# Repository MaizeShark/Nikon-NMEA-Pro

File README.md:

# Nikon-NMEA-Pro

A low-power GNSS logger and BLE remote shutter for Nikon cameras with the 10-pin connector. It is a work in progress: the hardware is designed, the PCB has not been built or tested, and the firmware has not been started.

<p align="center"><em>Front (left) and back (right) of the PCB.</em></p>

## Goals

Older GPS units for Nikon cameras (GP-1, Solmeta GMAX) typically draw tens of mA continuously, are slow to get a cold fix, and have no wireless connectivity. This 35 x 35 mm module aims to improve on them:

- Standby draw of tens of µA instead of tens of mA
- Fast fixes by injecting assistance data (u-blox AssistNow) from a smartphone over BLE
- Four-constellation tracking with a u-blox M10 receiver
- BLE remote shutter and USB-C file access

| Status | Item |
| :--- | :--- |
| Done | Schematic and PCB layout |
| Pending | PCB fabrication and assembly |
| Pending | Power measurements (all current figures below are datasheet estimates) |
| Not started | Firmware |

## Camera connection

> [!NOTE]
> I connect the module to my Nikon D200 using a **Nikon MC-35 cable** (GPS adapter cable for RS232). I have not verified compatibility with other bodies or cables.

## Planned features

- **EXIF geotagging:** convert GNSS position and barometric altitude into 5 V TTL NMEA sentences for the camera.
- **Hot-shoe X-sync logging:** read the X-sync contact and write a `<wpt>` tag to the GPX log when the shutter fires.
- **Motion-aware track logging:** log GPX tracks to a 16 MB SPI NOR flash chip, pausing when the accelerometer shows the camera is stationary.
- **USB-C mass storage:** mount as a flash drive for drag-and-drop GPX access.
- **BLE remote:** trigger autofocus and shutter release from a smartphone app via MOSFET outputs.
- **Auto-wake:** monitor `V_CC` on the 10-pin connector and wake from System OFF when the camera powers on.

## Hardware

### Processing and communications

| Function | Part | Notes |
| :--- | :--- | :--- |
| MCU | u-blox BMD-340-A-R (nRF52840) | BLE, USB MSC, sensor fusion, NMEA generation |
| Level shifting | TI TXU0202 | 3V3 -> 5V for Camera UART |

### GNSS and sensors

- **Receiver:** u-blox MAX-M10S (GPS, Galileo, GLONASS, BeiDou concurrently).
- **Antenna:** active antenna on a U.FL connector, powered through a bias-T. A MOSFET driven by `LNA_EN` cuts antenna power when the GNSS is asleep.
- **Compass:** ST LSM303AGR (I2C), for tilt-compensated heading in `$--HDG` sentences.
- **Barometer:** Bosch BMP581 (I2C), for altitude.

### Power

The board can be powered from USB (5 V) or the camera (`V_BAT`, up to 8.4 V).

- **Source selection:** Nexperia BAV170 dual diode, chosen for very low reverse leakage to prevent backfeed.
- **Regulation:** TI TPS70933 3.3 V LDO. Accepts inputs above 30 V with about 1 µA quiescent current.
- **Backup:** Seiko MS621FE rechargeable coin cell, trickle-charged in normal use. It is intended to keep the u-blox RTC and orbital data alive for a few days with the camera battery removed, preserving fast fixes after a battery swap (about 4.5 days estimated).

## PCB

- **Size:** 35 x 35 mm, 4 layers.
- **Stackup:** JLC04161H-3313 (0.09 mm dielectric between L1 and L2).
- **RF:** 50 Ω coplanar waveguide with ground (CPWG) for the 1.5 GHz GNSS path.

### Assembly

Components are on both sides, so assembly is planned as two-stage soldering to keep the bottom side from shifting:

1. Bottom side (including hidden LGA pads): lead-free paste, reflowed on a hot plate at ~220 °C.
2. Top side: leaded paste, hot air at ~183 °C, below the bottom side's solidus so those joints stay solid.

## Estimated power budget

These are summed datasheet typical values, not measurements.

| State | Component | Current |
| :--- | :--- | :--- |
| Sleep | nRF52840 (System OFF) | ~1.0 µA |
| Sleep | MAX-M10S (software standby) | ~46.0 µA |
| Sleep | `V_BAT` ADC divider (3.2 MΩ) | ~2.6 µA |
| Sleep | I2C sensors, flash, LDO quiescent | ~3.8 µA |
| | **Total standby (estimated)** | **~53.4 µA** |
| Active | Full system (BLE, 4-GNSS, sensors, USB) | **~22 mA** |

At roughly 53 µA, standby would take over 3 years to drain a 1500 mAh battery, ignoring the battery's own self-discharge. Real numbers will be measured once the board is built.

## Firmware

Not started. The plan is Zephyr RTOS, with hardware interrupt handling, LittleFS wear leveling on the SPI flash, BLE GATT profiles, and USB mass storage.

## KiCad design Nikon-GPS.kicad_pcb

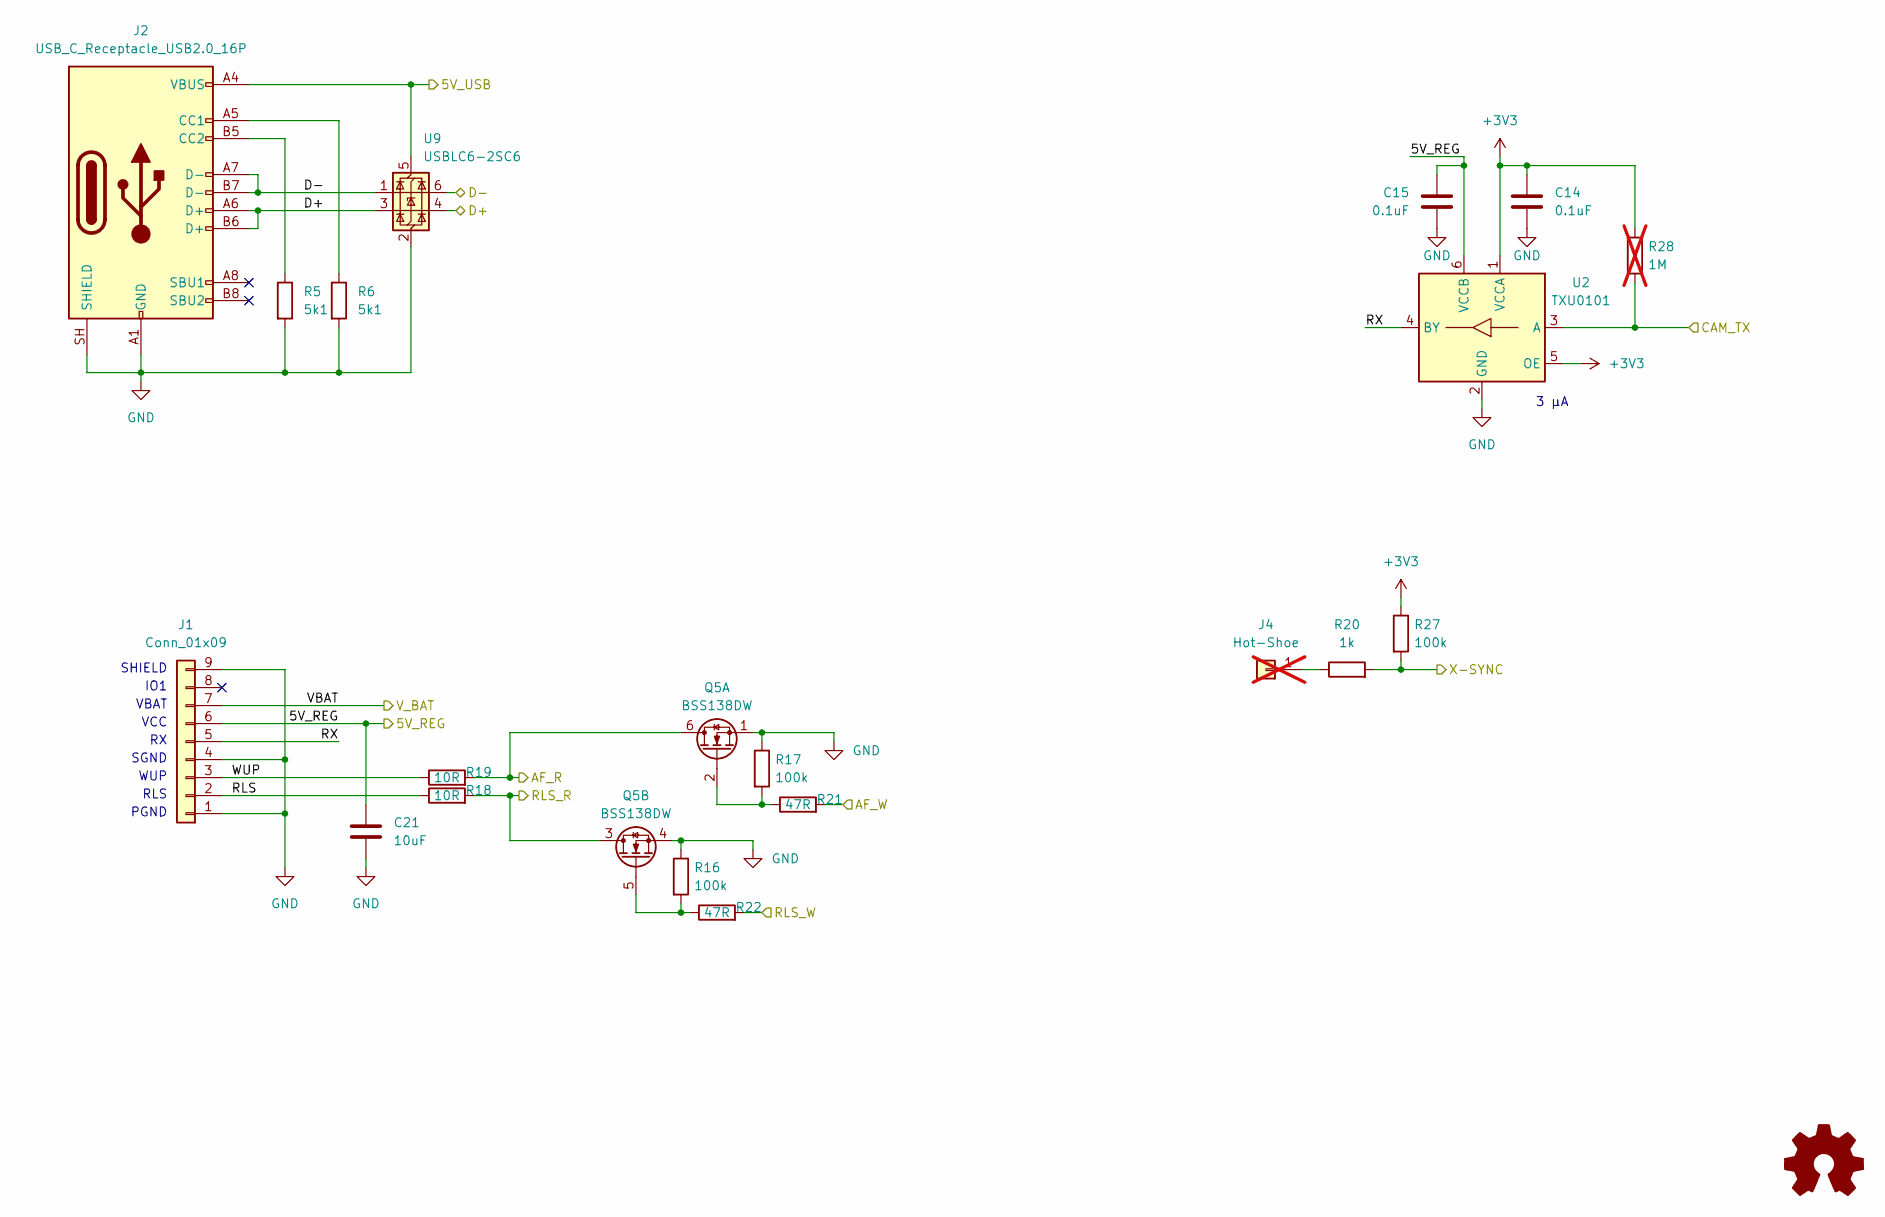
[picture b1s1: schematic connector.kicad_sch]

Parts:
C14, C15: 0.1uF; C_0402_1005Metric; LCSC C77020
C21: 10uF; C_0805_2012Metric; LCSC C32635
J1: Conn_01x09; Nikon Connector
J2: USB_C_Receptacle_USB2.0_16P; USB_C_Receptacle_G-Switch_GT-USB-7010ASV; LCSC C2988369
J4: Hot-Shoe; PinHeader_1x01_P2.54mm_Vertical; not fitted
Q5: BSS138DW; SOT-363_SC-70-6; LCSC C154900
R5, R6: 5k1; R_0402_1005Metric; LCSC C105872
R16, R17, R27: 100k; R_0402_1005Metric; LCSC C60491
R18, R19: 10R; R_0603_1608Metric; LCSC C109318
R20: 1k; R_0402_1005Metric; LCSC C106235
R21, R22: 47R; R_0402_1005Metric; LCSC C137973
R28: 1M; R_0402_1005Metric; LCSC C138033; not fitted
U2: TXU0101; Texas_DCK0006A_2.1x2mm_P0.65mm; LCSC C5217868
U9: USBLC6-2SC6; SOT-23-6; LCSC C5261088

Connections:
+3V3: C14.1, R27.1, R28.1, U2.1 (VCCA), U2.5 (OE); also elsewhere on the board
/Connector/5V_REG: C15.1, C21.1, J1.6, U2.6 (VCCB); also elsewhere on the board
/Connector/5V_USB: J2.A4 (VBUS), J2.A9 (VBUS), J2.B4 (VBUS), J2.B9 (VBUS), U9.5 (VBUS); also elsewhere on the board
/Connector/AF_R: Q5.6 (D1), R19.2; also elsewhere on the board
/Connector/AF_W: R21.2; also elsewhere on the board
/Connector/CAM_TX: R28.2, U2.3 (A); also elsewhere on the board
/Connector/D+: J2.A6 (D+), J2.B6 (D+), U9.3 (I/O2), U9.4 (I/O2); also elsewhere on the board
/Connector/D-: J2.A7 (D-), J2.B7 (D-), U9.1 (I/O1), U9.6 (I/O1); also elsewhere on the board
/Connector/RLS: J1.2, R18.1
/Connector/RLS_R: Q5.3 (D2), R18.2; also elsewhere on the board
/Connector/RLS_W: R22.2; also elsewhere on the board
/Connector/RX: J1.5, U2.4 (BY)
/Connector/VBAT: J1.7; also elsewhere on the board
/Connector/WUP: J1.3, R19.1
/Connector/X-SYNC: R20.2, R27.2; also elsewhere on the board
GND: C14.2, C15.2, C21.2, J1.1, J1.4, J1.9, J2.A1 (GND), J2.A12 (GND), J2.B1 (GND), J2.B12 (GND), J2.SH (SHIELD), Q5.1 (S1), Q5.4 (S2), R5.2, R6.2, R16.1, R17.1, U2.2 (GND), U9.2 (GND); also elsewhere on the board
unnamed: J2.A5 (CC1), R6.1
unnamed: J2.B5 (CC2), R5.1
unnamed: J4.1 (Pin_1_1), R20.1
unnamed: Q5.2 (G1), R17.2, R21.1
unnamed: Q5.5 (G2), R16.2, R22.1

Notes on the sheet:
VBAT
WUP
RLS
PGND
IO1
3 μA
SGND
SHIELD
VCC

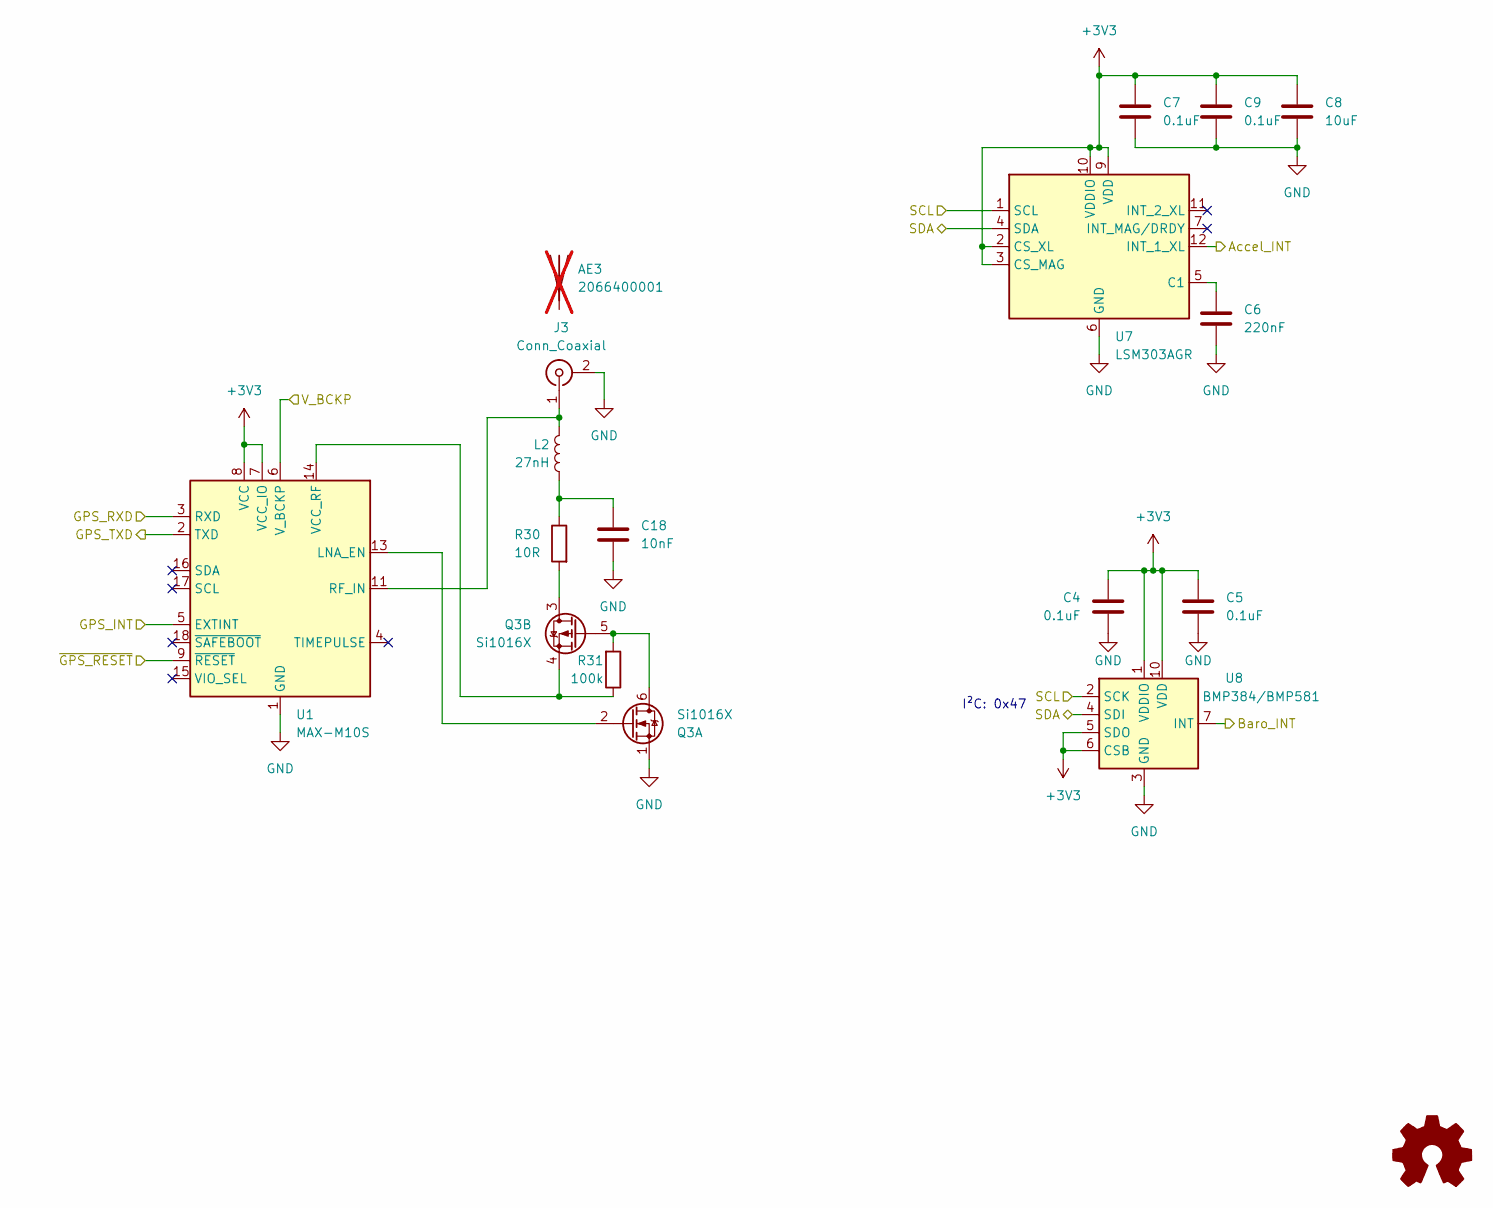
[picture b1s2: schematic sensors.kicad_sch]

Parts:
AE3: 2066400001; 2042860001; LCSC C841211; not fitted
C4, C5, C7, C9: 0.1uF; C_0402_1005Metric; LCSC C77020
C6: 220nF; C_0402_1005Metric; LCSC C696846
C8: 10uF; C_0603_1608Metric; LCSC C19702
C18: 10nF; C_0402_1005Metric; LCSC C85735
J3: Conn_Coaxial; U.FL_Molex_MCRF_73412-0110_Vertical; LCSC C41375966
L2: 27nH; L_0402_1005Metric; LCSC C12669
Q3: Si1016X; SOT-563; LCSC C50314620
R30: 10R; R_0402_1005Metric; LCSC C138066
R31: 100k; R_0402_1005Metric; LCSC C60491
U1: MAX-M10S; ublox_MAX; LCSC C4153167
U7: LSM303AGR; LGA-12_2x2mm_P0.5mm; LCSC C126671
U8: BMP384/BMP581; Bosch_WFLGA-10_2x2mm_P0.5mm; LCSC C5362283

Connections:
+3V3: C4.1, C5.1, C7.1, C8.1, C9.1, U1.7 (VCC_IO), U1.8 (VCC), U7.2 (CS_XL), U7.3 (CS_MAG), U7.9 (VDD), U7.10 (VDDIO), U8.1 (VDDIO), U8.5 (SDO), U8.6 (CSB), U8.10 (VDD); also elsewhere on the board
/MCU/Accel_INT: U7.12 (INT_1_XL); also elsewhere on the board
/MCU/Baro_INT: U8.7 (INT); also elsewhere on the board
/MCU/GPS_INT: U1.5 (EXTINT); also elsewhere on the board
/MCU/GPS_RXD: U1.2 (TXD); also elsewhere on the board
/MCU/GPS_TXD: U1.3 (RXD); also elsewhere on the board
/MCU/SCL: U7.1 (SCL), U8.2 (SCK); also elsewhere on the board
/MCU/SDA: U7.4 (SDA), U8.4 (SDI); also elsewhere on the board
/MCU/~GPS_RESET: U1.9 (~RESET); also elsewhere on the board
/Power/V_BCKP: U1.6 (V_BCKP); also elsewhere on the board
GND: C4.2, C5.2, C6.2, C7.2, C8.2, C9.2, C18.2, J3.2 (Ext), Q3.1 (SN), U1.1 (GND), U1.10 (GND), U1.12 (GND), U7.6 (GND), U7.8 (GND), U8.3 (GND), U8.8 (GND), U8.9 (GND), U8.[8,9] (GND); also elsewhere on the board
unnamed: C18.1, L2.2, R30.1
unnamed: J3.1 (In), L2.1, U1.11 (RF_IN)
unnamed: Q3.5 (GP), Q3.6 (DN), R31.2
unnamed: Q3.2 (GN), U1.13 (LNA_EN)
unnamed: Q3.3 (DP), R30.2
unnamed: Q3.4 (SP), R31.1, U1.14 (VCC_RF)
unnamed: C6.1, U7.5 (C1)

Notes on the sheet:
I²C: 0x47

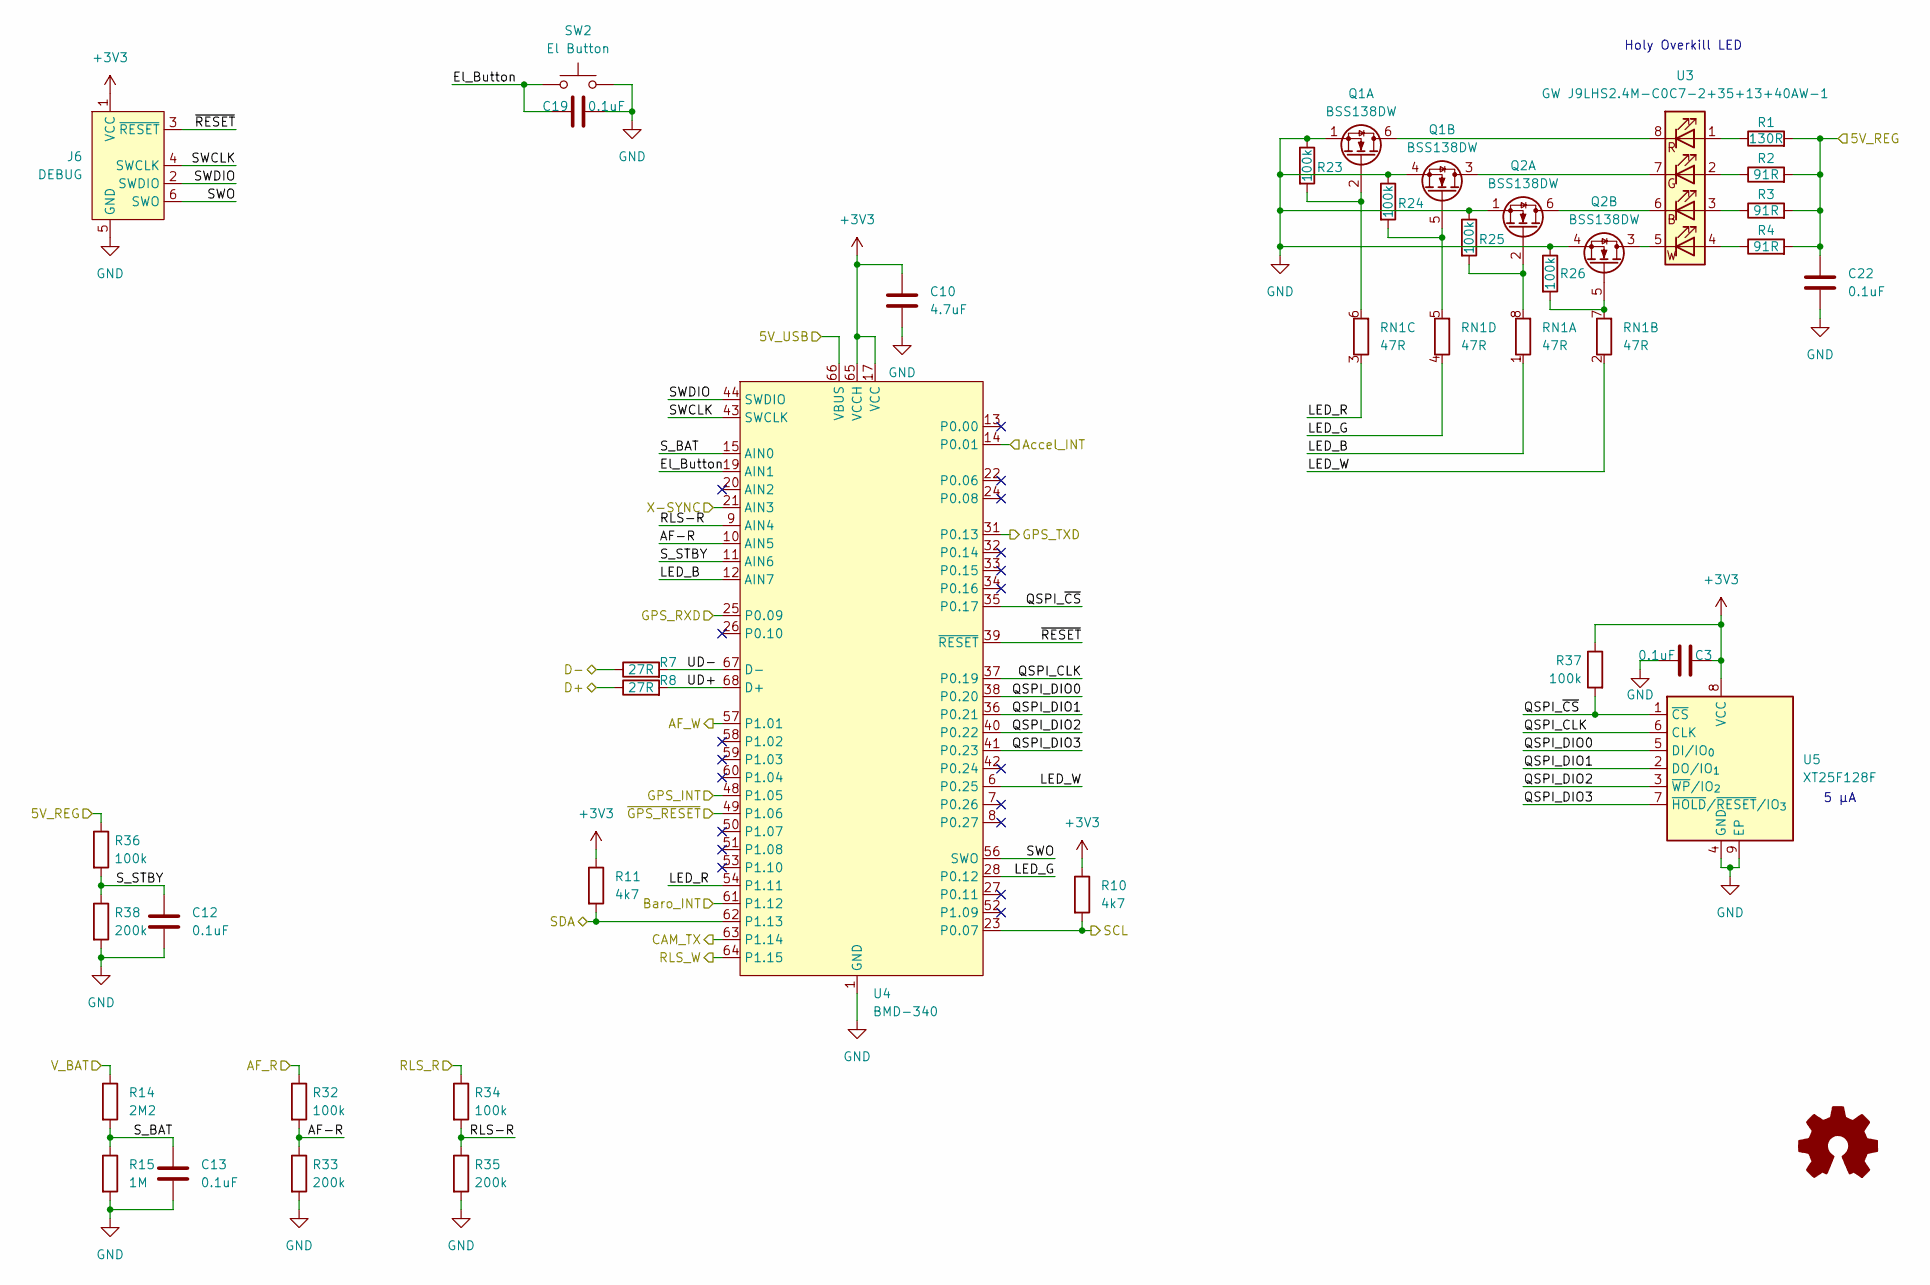
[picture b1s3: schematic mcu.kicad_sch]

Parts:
C3, C12, C13, C19, C22: 0.1uF; C_0402_1005Metric; LCSC C77020
C10: 4.7uF; C_0603_1608Metric; LCSC C1705
J6: DEBUG; Tag-Connect_TC2030-IDC-NL_2x03_P1.27mm_Vertical
Q1, Q2: BSS138DW; SOT-363_SC-70-6; LCSC C154900
R1: 130R; R_0402_1005Metric; LCSC C413066
R2, R3, R4: 91R; R_0402_1005Metric; LCSC C2998110
R7, R8: 27R; R_0402_1005Metric; LCSC C2909343
R10, R11: 4k7; R_0402_1005Metric; LCSC C105871
R14: 2M2; R_0402_1005Metric; LCSC C2998080
R15: 1M; R_0402_1005Metric; LCSC C138033
R23, R24, R25, R26, R32, R34, R36, R37: 100k; R_0402_1005Metric; LCSC C60491
R33, R35, R38: 200k; R_0402_1005Metric; LCSC C2906866
RN1: 47R; R_Array_Convex_4x0603; LCSC C16081
SW2: El Button; SKSUAAE010
U3: GW J9LHS2.4M-C0C7-2+35+13+40AW-1; GW J9LHS2.4M; LCSC C5648656
U4: BMD-340; LCSC C5456944
U5: XT25F128F; WSON-8-1EP_6x5mm_P1.27mm_EP3.4x4mm; LCSC C3202839

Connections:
+3V3: C3.2, C10.1, J6.1 (VCC), R10.1, R11.1, R37.1, U4.17 (VCC), U4.65 (VCCH), U5.8 (VCC); also elsewhere on the board
/Connector/5V_REG: C22.1, R1.2, R2.2, R3.2, R4.2, R36.1; also elsewhere on the board
/Connector/5V_USB: U4.66 (VBUS); also elsewhere on the board
/Connector/AF_R: R32.1; also elsewhere on the board
/Connector/AF_W: U4.57 (P1.01); also elsewhere on the board
/Connector/CAM_TX: U4.63 (P1.14); also elsewhere on the board
/Connector/D+: R8.1; also elsewhere on the board
/Connector/D-: R7.1; also elsewhere on the board
/Connector/RLS_R: R34.1; also elsewhere on the board
/Connector/RLS_W: U4.64 (P1.15); also elsewhere on the board
/Connector/VBAT: R14.1; also elsewhere on the board
/Connector/X-SYNC: U4.21 (AIN3); also elsewhere on the board
/MCU/AF-R: R32.2, R33.1, U4.10 (AIN5)
/MCU/Accel_INT: U4.14 (P0.01); also elsewhere on the board
/MCU/Baro_INT: U4.61 (P1.12); also elsewhere on the board
/MCU/El_Button: C19.1, SW2.1, U4.19 (AIN1)
/MCU/GPS_INT: U4.48 (P1.05); also elsewhere on the board
/MCU/GPS_RXD: U4.25 (P0.09); also elsewhere on the board
/MCU/GPS_TXD: U4.31 (P0.13); also elsewhere on the board
/MCU/LED_B: RN1.1 (R1.1), U4.12 (AIN7)
/MCU/LED_G: RN1.4 (R4.1), U4.28 (P0.12)
/MCU/LED_R: RN1.3 (R3.1), U4.54 (P1.11)
/MCU/LED_W: RN1.2 (R2.1), U4.6 (P0.25)
/MCU/QSPI_CLK: U4.37 (P0.19), U5.6 (CLK)
/MCU/QSPI_DIO0: U4.38 (P0.20), U5.5 (DI/IO_{0})
/MCU/QSPI_DIO1: U4.36 (P0.21), U5.2 (DO/IO_{1})
/MCU/QSPI_DIO2: U4.40 (P0.22), U5.3 (~WP/IO_{2})
/MCU/QSPI_DIO3: U4.41 (P0.23), U5.7 (~HOLD/~RESET/IO_{3})
/MCU/QSPI_~CS: R37.2, U4.35 (P0.17), U5.1 (~CS)
/MCU/RLS-R: R34.2, R35.1, U4.9 (AIN4)
/MCU/SCL: R10.2, U4.23 (P0.07); also elsewhere on the board
/MCU/SDA: R11.2, U4.62 (P1.13); also elsewhere on the board
/MCU/SWCLK: J6.4 (SWCLK), U4.43 (SWCLK)
/MCU/SWDIO: J6.2 (SWDIO), U4.44 (SWDIO)
/MCU/SWO: J6.6 (SWO), U4.56 (SWO)
/MCU/S_BAT: C13.1, R14.2, R15.1, U4.15 (AIN0)
/MCU/S_STBY: C12.1, R36.2, R38.1, U4.11 (AIN6)
/MCU/UD+: R8.2, U4.68 (D+)
/MCU/UD-: R7.2, U4.67 (D-)
/MCU/~GPS_RESET: U4.49 (P1.06); also elsewhere on the board
/MCU/~RESET: J6.3 (~RESET), U4.39 (~RESET)
GND: C3.1, C10.2, C12.2, C13.2, C19.2, C22.2, J6.5 (GND), Q1.1 (S1), Q1.4 (S2), Q2.1 (S1), Q2.4 (S2), R15.2, R23.1, R24.1, R25.1, R26.1, R33.2, R35.2, R38.2, SW2.2, U4.1 (GND), U4.2 (GND), U4.3 (GND), U4.4 (GND), U4.5 (GND), U4.16 (GND), U4.18 (GND), U4.29 (GND), U4.30 (GND), U4.45 (GND), U4.46 (GND), U4.47 (GND), U4.55 (GND), U4.[2-5,16,18,29,30,45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 (GND), U5.4 (GND), U5.9 (EP); also elsewhere on the board
unnamed: Q1.6 (D1), U3.8 (RK)
unnamed: Q1.2 (G1), R23.2, RN1.6 (R3.2)
unnamed: Q1.3 (D2), U3.7 (GK)
unnamed: Q1.5 (G2), R24.2, RN1.5 (R4.2)
unnamed: Q2.6 (D1), U3.6 (BK)
unnamed: Q2.2 (G1), R25.2, RN1.8 (R1.2)
unnamed: Q2.3 (D2), U3.5 (WK)
unnamed: Q2.5 (G2), R26.2, RN1.7 (R2.2)
unnamed: R3.1, U3.3 (BA)
unnamed: R2.1, U3.2 (GA)
unnamed: R1.1, U3.1 (RA)
unnamed: R4.1, U3.4 (WA)

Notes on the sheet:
Holy Overkill LED
5 μA

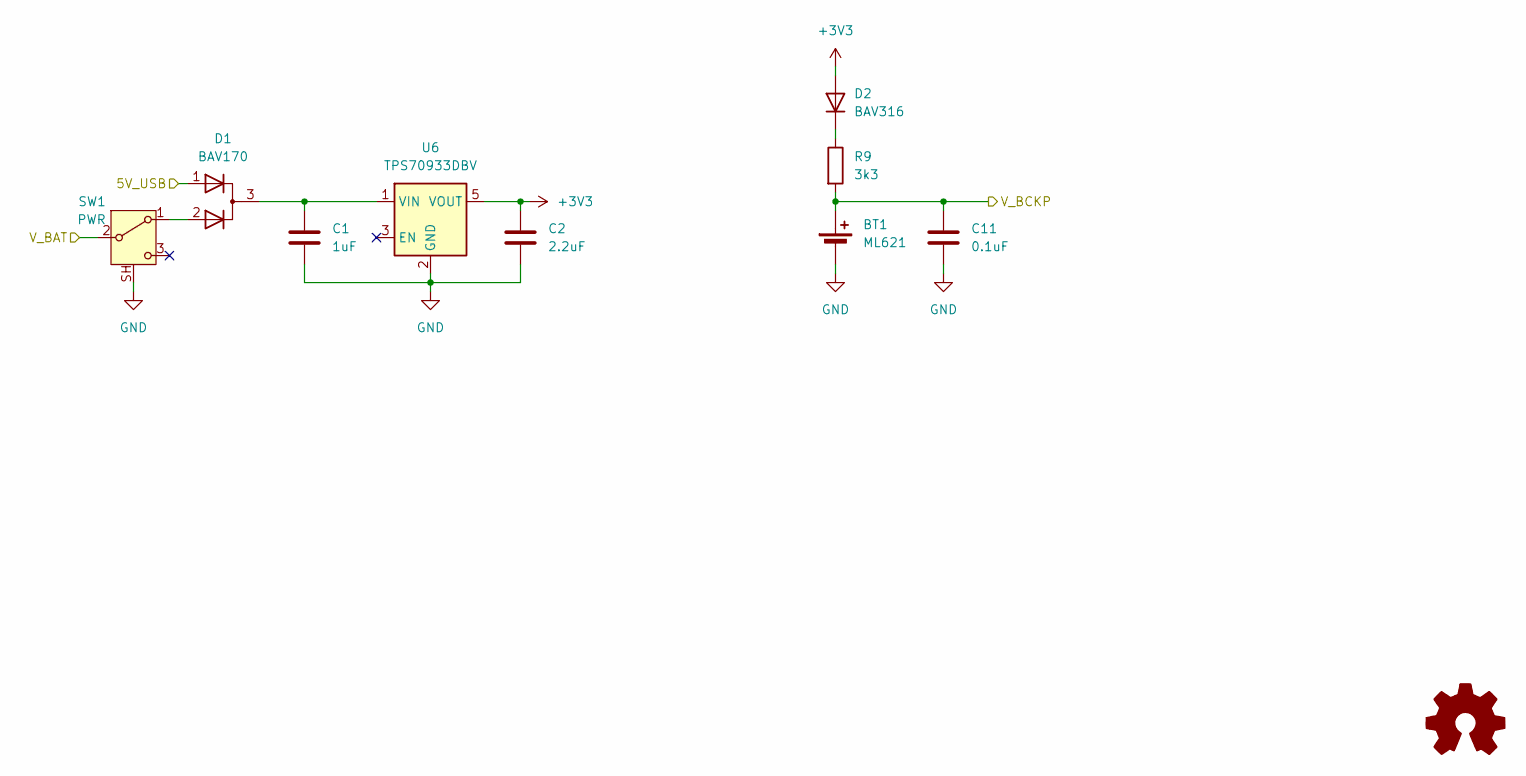
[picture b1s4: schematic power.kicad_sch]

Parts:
BT1: ML621; Battery_Panasonic_ML621_Vertical
C1: 1uF; C_0805_2012Metric; LCSC C344178
C2: 2.2uF; C_0603_1608Metric; LCSC C57895
C11: 0.1uF; C_0402_1005Metric; LCSC C77020
D1: BAV170; SOT-23; LCSC C109309
D2: BAV316; D_SOD-323; LCSC C3031914
R9: 3k3; R_0603_1608Metric; LCSC C22978
SW1: PWR; SW_SPDT_Shouhan_MSK12C02; LCSC C2681566
U6: TPS70933DBV; SOT-23-5_HandSoldering; LCSC C90991

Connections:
+3V3: C2.1, D2.2 (A), U6.5 (VOUT); also elsewhere on the board
/Connector/5V_USB: D1.1 (A); also elsewhere on the board
/Connector/VBAT: SW1.2 (B); also elsewhere on the board
/Power/V_BCKP: BT1.1 (+), C11.1, R9.2; also elsewhere on the board
GND: BT1.2 (-), C1.2, C2.2, C11.2, SW1.SH (MP), U6.2 (GND); also elsewhere on the board
unnamed: C1.1, D1.3 (K), U6.1 (VIN)
unnamed: D2.1 (K), R9.1
unnamed: D1.2 (A), SW1.1 (A)

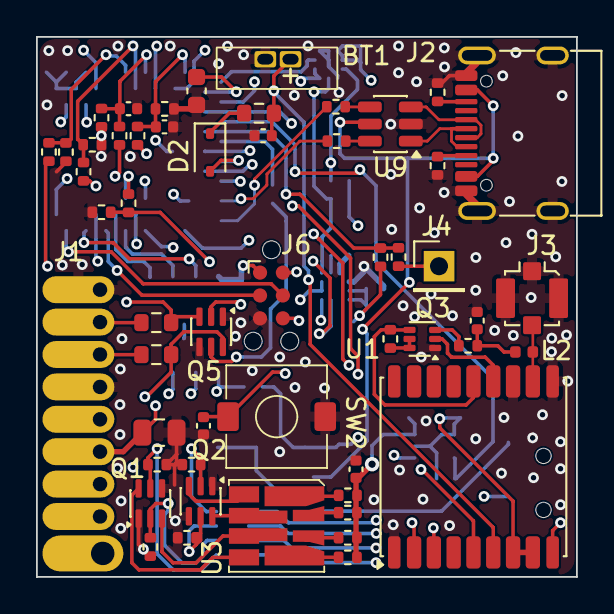
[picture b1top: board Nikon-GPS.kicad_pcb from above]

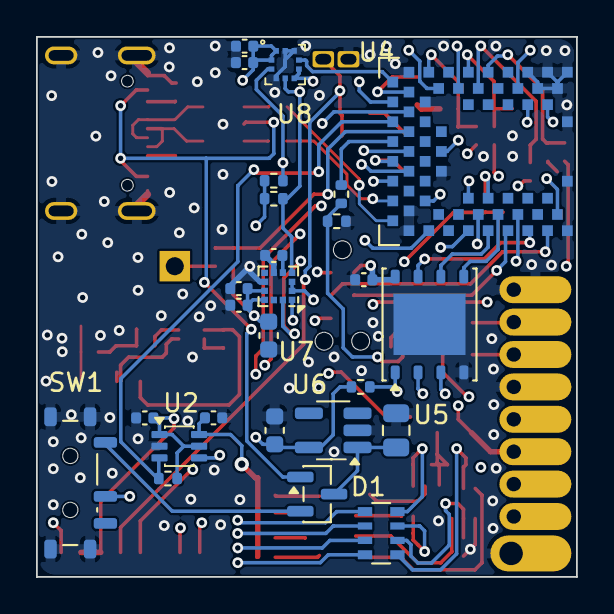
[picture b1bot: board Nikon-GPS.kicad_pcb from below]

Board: 4 copper layers, 30.0 x 30.0 mm, 79 parts (26 on the bottom side), 73 nets.
